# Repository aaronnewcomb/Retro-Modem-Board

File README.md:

# Retro-Modem-Board
This is the PCB I built to be used with the Zmodem project

This boards uses an ESP8266 in the form of an ESP-12E/F module along with some simple parts to act as a modem/wifi bridge. It was initially built to be used with this Zmodem project. https://github.com/bozimmerman/Zimodem

3D printable case available here https://www.thingiverse.com/thing:4876405
## Video

## BOM

\*All caps and resistors are 0805/2012
Label | Part
------------ | -------------
C1, C2 | 10uF Capacitor
C3 - C7 | .1uF Capacitor
D1 | 0805 LED
J1 | USB Micro-B socket
J2 | 9 Pin Female DSUB 4.94mm Edge Pin Offset
J3 | 02x06 Pin Header
R1 | 470 Ohm Resistor
R2 - R5 | 1K Ohm Resistor
SW1, SW2 | Push Button Right Angle
U1 | NCP1117ST33T3G
U2 | MAX3232
U3 | ESP-12E/F Module

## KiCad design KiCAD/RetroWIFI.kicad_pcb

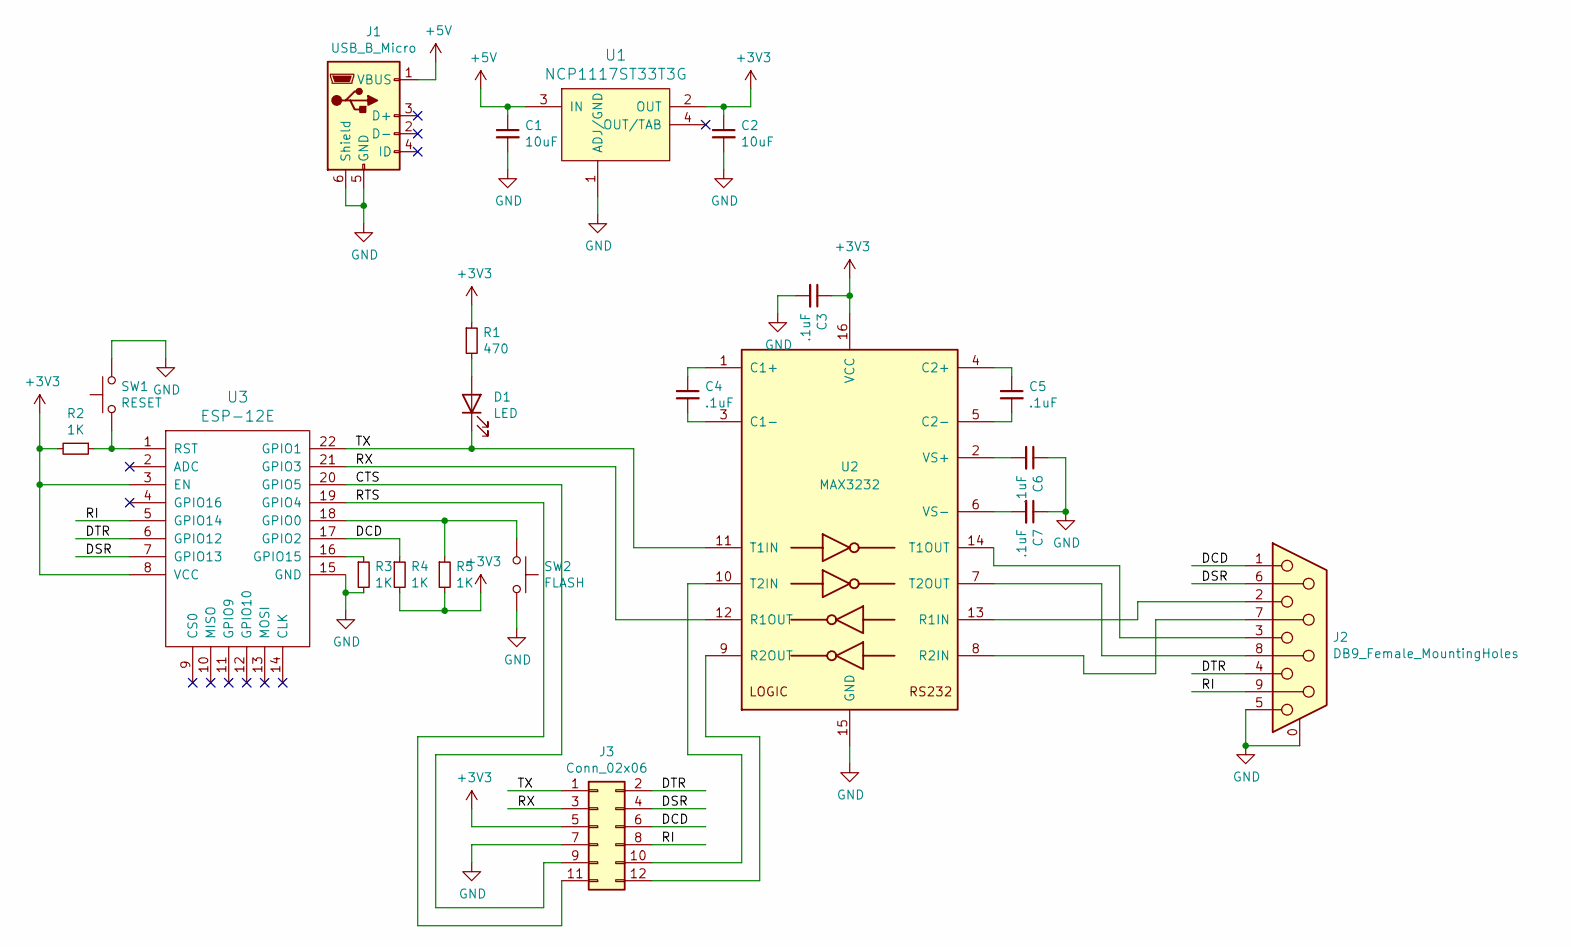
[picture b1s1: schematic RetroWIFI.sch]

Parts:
C1, C2: 10uF; C_0805_2012Metric
C3, C4, C5, C6, C7: .1uF; C_0805_2012Metric
D1: LED; LED_0805_2012Metric
J1: USB_B_Micro; USB_Micro-B_Wuerth_629105150521
J2: DB9_Female_MountingHoles; DSUB-9_Female_Horizontal_P2.77x2.84mm_EdgePinOffset4.94mm_H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
J3: Conn_02x06; PinHeader_2x06_P2.54mm_Vertical
R1: 470; R_0805_2012Metric
R2, R3, R4, R5: 1K; R_0805_2012Metric
SW1: RESET; SW_Tactile_SKHH_Angled
SW2: FLASH; SW_Tactile_SKHH_Angled
U1: NCP1117ST33T3G; SOT-223; MPN NCP1117ST33T3G; Digi-Key_PN NCP1117ST33T3GOSCT-ND
U2: MAX3232; SOIC-16_3.9x9.9mm_P1.27mm
U3: ESP-12E

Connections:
+3V3: C2.1, C3.1, J3.5, R1.1, R2.2, R4.2, R5.2, U1.2 (OUT), U2.16 (VCC), U3.3 (EN), U3.8 (VCC)
+5V: C1.1, J1.1 (VBUS), U1.3 (IN)
/CTS: J3.9, U3.20 (GPIO5)
/DCD: J2.1, J3.6, R4.1, U3.17 (GPIO2)
/DSR: J2.6, J3.4, U3.7 (GPIO13)
/DTR: J2.4, J3.2, U3.6 (GPIO12)
/RI: J2.9, J3.8, U3.5 (GPIO14)
/RTS: J3.11, U3.19 (GPIO4)
/RX: J3.3, U2.12 (R1OUT), U3.21 (GPIO3)
/TX: D1.1 (K), J3.1, U2.11 (T1IN), U3.22 (GPIO1)
GND: C1.2, C2.2, C3.2, C6.1, C7.1, J1.5 (GND), J1.6 (Shield), J2.0 (PAD), J2.5, J3.7, R3.2, SW1.2, SW2.2, U1.1 (ADJ/GND), U2.15 (GND), U3.15 (GND)
unnamed: C4.1, U2.1 (C1+)
unnamed: C4.2, U2.3 (C1-)
unnamed: C5.1, U2.4 (C2+)
unnamed: C5.2, U2.5 (C2-)
unnamed: C6.2, U2.2 (VS+)
unnamed: C7.2, U2.6 (VS-)
unnamed: D1.2 (A), R1.2
unnamed: J2.2, U2.13 (R1IN)
unnamed: J2.3, U2.14 (T1OUT)
unnamed: J2.7, U2.8 (R2IN)
unnamed: J2.8, U2.7 (T2OUT)
unnamed: J3.10, U2.10 (T2IN)
unnamed: J3.12, U2.9 (R2OUT)
unnamed: R2.1, SW1.1, U3.1 (RST)
unnamed: R3.1, U3.16 (GPIO15)
unnamed: R5.1, SW2.1, U3.18 (GPIO0)

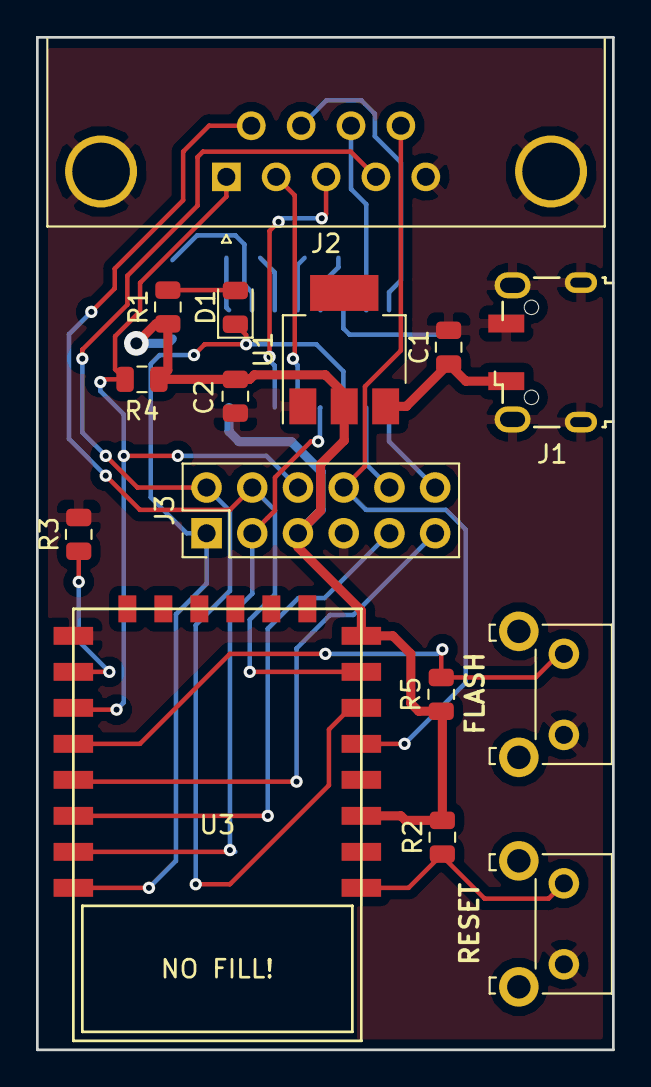
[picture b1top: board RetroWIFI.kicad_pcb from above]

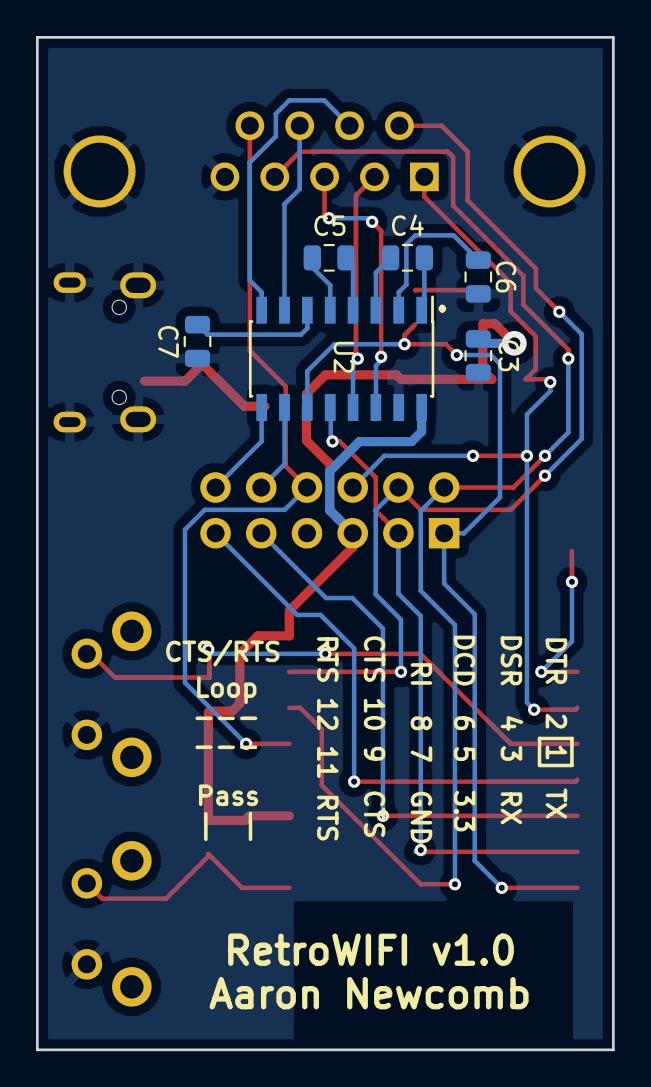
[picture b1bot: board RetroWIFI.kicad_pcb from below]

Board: 2 copper layers, 32.0 x 56.2 mm, 21 parts (6 on the bottom side), 27 nets.

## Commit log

2021-06-01 Initail file upload
2021-06-01 Create temp
2021-06-01 Initial file upload
2021-06-01 Added BOM
